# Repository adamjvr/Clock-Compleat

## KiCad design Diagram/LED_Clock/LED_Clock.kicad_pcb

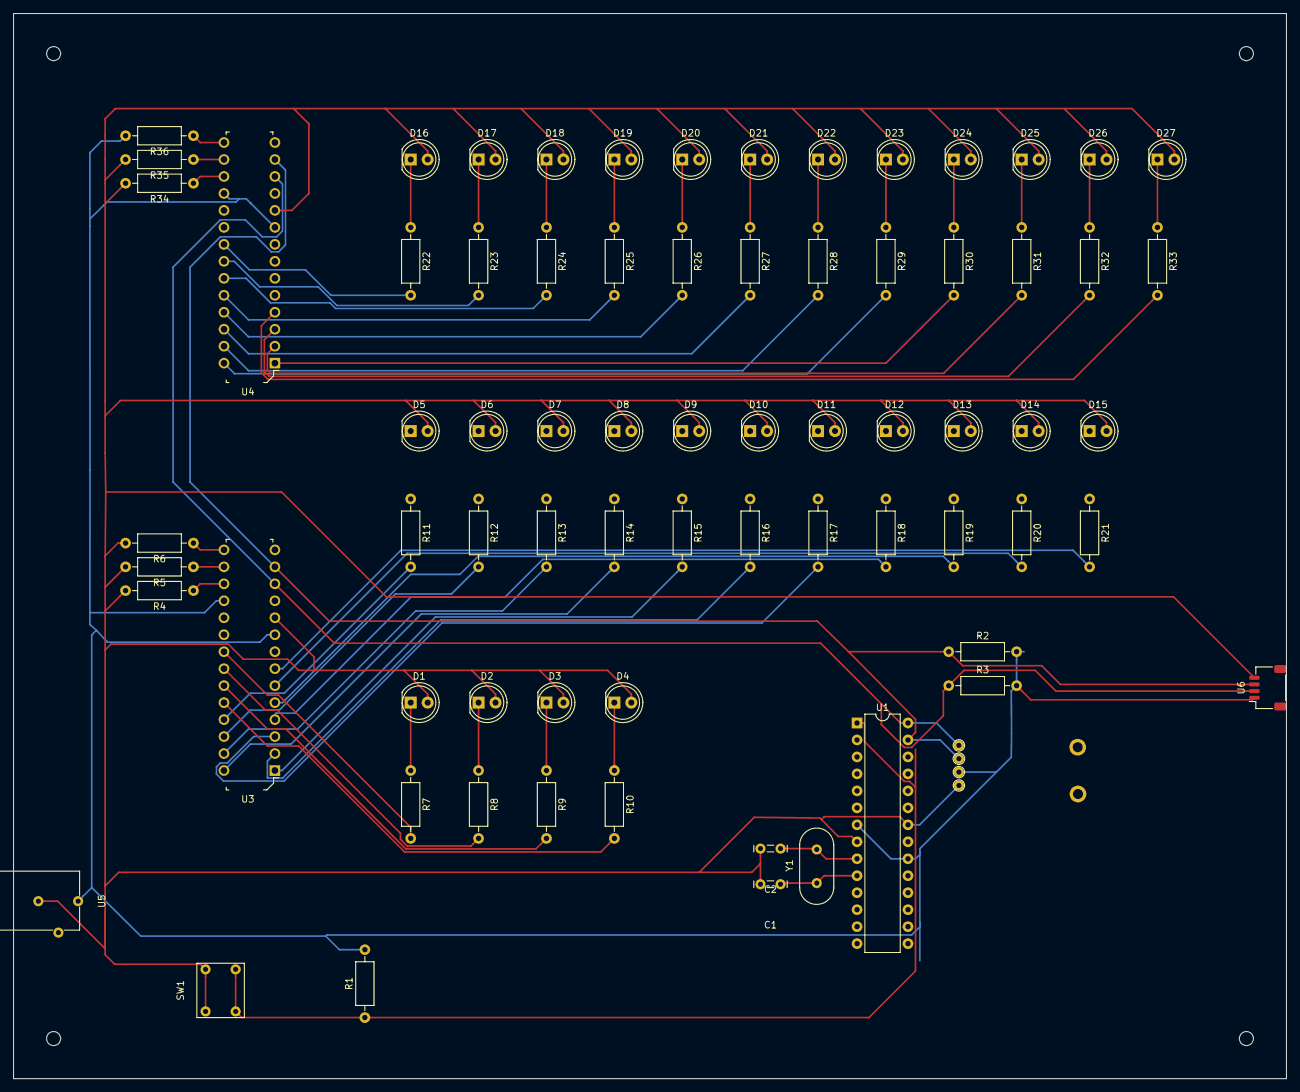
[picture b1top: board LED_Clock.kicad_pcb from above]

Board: 2 copper layers, 190.5 x 159.4 mm, 73 parts (0 on the bottom side), 67 nets.

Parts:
C1, C2: Capacitor
D1, D2, D3, D4, D5, D6, D7, D8, D9, D10, D11, D12, D13, D14, D15, D16, D17, D18, D19, D20, D21, D22, D23, D24, D25, D26, D27: Blue; LED_D5.0mm
R1, R4, R5, R6, R7, R8, R9, R10, R11, R12, R13, R14, R15, R16, R17, R18, R19, R20, R21, R22, R23, R24, R25, R26, R27, R28, R29, R30, R31, R32, R33, R34, R35, R36: 1k; R_Axial_DIN0207_L6.3mm_D2.5mm_P10.16mm_Horizontal
R2, R3: 4.7k; R_Axial_DIN0207_L6.3mm_D2.5mm_P10.16mm_Horizontal
SW1: SW_Push_Dual; Pushbutton
U1: ATmega328P-PU; DIP-28_W7.62mm
U2: DS3231MZ; DS3231
U3, U4: MCP23017-E_SP; DIP-28_W7.62mm
U5: Barreljack; BarrelJack
U6: JST4pin; JST_SH_SM04B-SRSS-TB_1x04-1MP_P1.00mm_Horizontal
Y1: Crystal

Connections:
+5V: R1.2, R2.2, R3.2, R36.2, U1.7, U1.20, U2.2, U3.9, U3.18, U4.9, U4.18, U5.1, U6.1
/clock minute/SCL: R3.1, U1.28, U2.8, U3.12, U4.12, U6.2
/clock minute/SDA: R2.1, U1.27, U2.7, U3.13, U4.13, U6.3
GND: C1.2, C2.2, D1.2, D2.2, D3.2, D4.2, D5.2, D6.2, D7.2, D8.2, D9.2, D10.2, D11.2, D12.2, D13.2, D14.2, D15.2, D16.2, D17.2, D18.2, D19.2, D20.2, D21.2, D22.2, D23.2, D24.2, D25.2, D26.2, D27.2, R4.2, R5.2, R6.2, R34.2, R35.2, SW1.2, SW1.4, U1.8, U1.22, U2.5, U3.10, U4.10, U5.2, U6.4
GPB0: R15.2, U3.1
GPB1: R16.2, U3.2
GPB2: R17.2, U3.3
GPB3: R18.2, U3.4
GPB4: R19.2, U3.5
GPB5: R20.2, U3.6
GPB6: R21.2, U3.7
HGPB0: R30.2, U4.1
HGPB1: R31.2, U4.2
HGPB2: R32.2, U4.3
HGPB3: R33.2, U4.4
unnamed: C1.1, U1.10, Y1.1
unnamed: C2.1, U1.9, Y1.2
unnamed: D1.1, R7.1
unnamed: D2.1, R8.1
unnamed: D3.1, R9.1
unnamed: D4.1, R10.1
unnamed: D5.1, R11.1
unnamed: D6.1, R12.1
unnamed: D7.1, R13.1
unnamed: D8.1, R14.1
unnamed: D9.1, R15.1
unnamed: D10.1, R16.1
unnamed: D11.1, R17.1
unnamed: D12.1, R18.1
unnamed: D13.1, R19.1
unnamed: D14.1, R20.1
unnamed: D15.1, R21.1
unnamed: D16.1, R22.1
unnamed: D17.1, R23.1
unnamed: D18.1, R24.1
unnamed: D19.1, R25.1
unnamed: D20.1, R26.1
unnamed: D21.1, R27.1
unnamed: D22.1, R28.1
unnamed: D23.1, R29.1
unnamed: D24.1, R30.1
unnamed: D25.1, R31.1
unnamed: D26.1, R32.1
unnamed: D27.1, R33.1
unnamed: R1.1, SW1.1, SW1.3, U1.1
unnamed: R4.1, U3.17
unnamed: R5.1, U3.16
unnamed: R6.1, U3.15
unnamed: R7.2, U3.21
unnamed: R8.2, U3.22
unnamed: R9.2, U3.23
unnamed: R10.2, U3.24
unnamed: R11.2, U3.25
unnamed: R12.2, U3.26
unnamed: R13.2, U3.27
unnamed: R14.2, U3.28
unnamed: R22.2, U4.21
unnamed: R23.2, U4.22
unnamed: R24.2, U4.23
unnamed: R25.2, U4.24
unnamed: R26.2, U4.25
unnamed: R27.2, U4.26
unnamed: R28.2, U4.27
unnamed: R29.2, U4.28
unnamed: R34.1, U4.17
unnamed: R35.1, U4.16
unnamed: R36.1, U4.15

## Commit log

2020-04-09 Clock Compleat
2020-04-09 Ground Plane
    Added a ground plane and some traces.
